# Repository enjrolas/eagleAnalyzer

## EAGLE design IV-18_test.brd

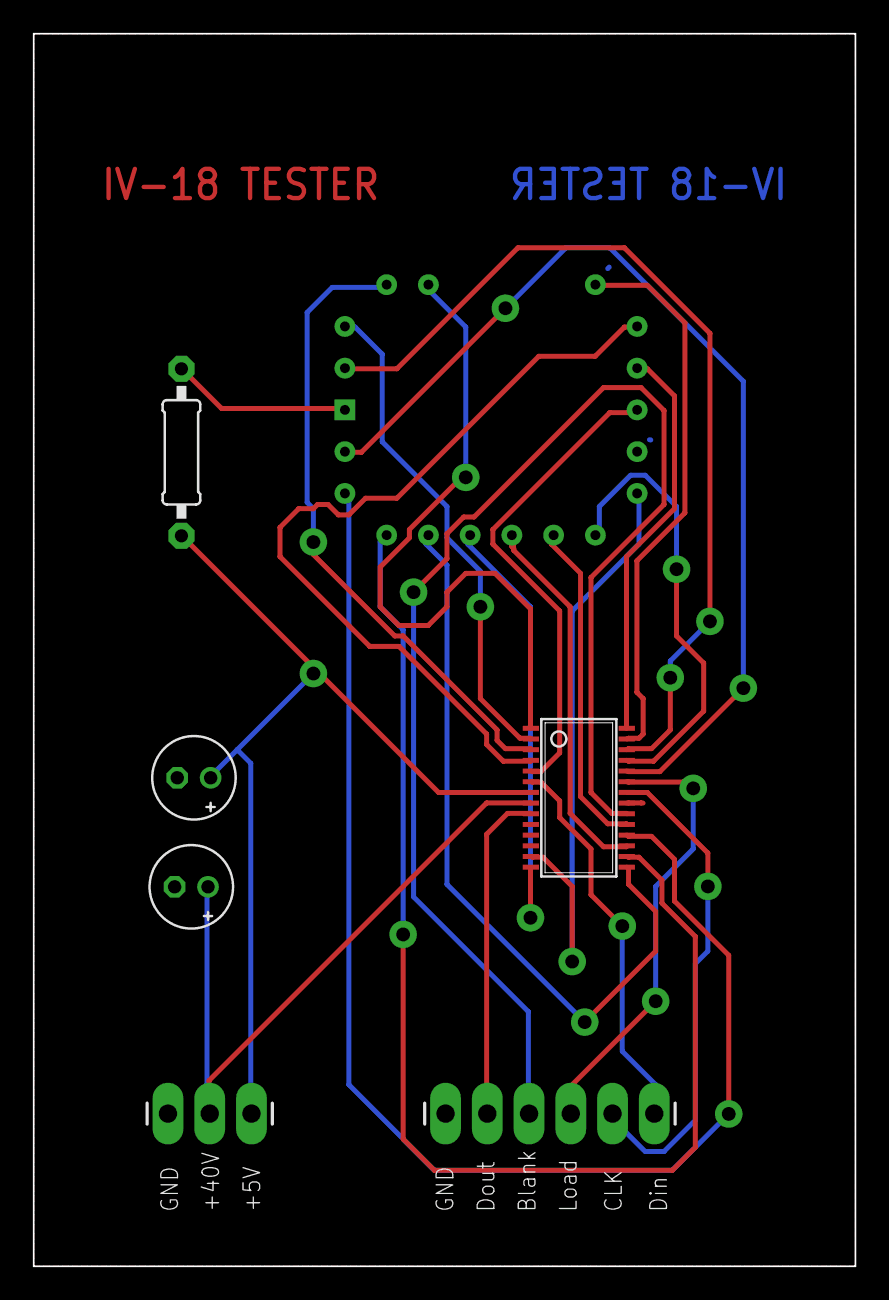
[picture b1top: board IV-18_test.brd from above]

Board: 2 copper layers, 50.0 x 75.0 mm, 7 parts (1 on the bottom side), 26 nets.

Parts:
C1: 10uF; E2-5
C2: 100nF; E2-5
DIS1: IV18-SQUARE; IV-18_SQUARE
JP1: 1X06_LONGPADS
JP2: 1X03_LONGPADS
R1: 56R; 0207/10
U$1: MAX6921AUI; TSSOP28

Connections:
GND: C1.-, C2.-, DIS1.13, JP1.1, JP2.1, U$1.21
unnamed: DIS1.12, U$1.5
unnamed: DIS1.10, U$1.4
unnamed: DIS1.4, U$1.3
unnamed: DIS1.3, U$1.2
unnamed: DIS1.5, U$1.1
unnamed: DIS1.11, U$1.28
unnamed: DIS1.9, U$1.27
unnamed: DIS1.2, U$1.26
unnamed: DIS1.15, U$1.25
unnamed: DIS1.22, U$1.24
unnamed: DIS1.16, U$1.19
unnamed: DIS1.21, U$1.18
unnamed: DIS1.17, U$1.17
unnamed: DIS1.20, U$1.16
unnamed: DIS1.19, U$1.15
unnamed: DIS1.18, U$1.14
unnamed: DIS1.14, U$1.13
unnamed: JP1.6, U$1.6
unnamed: JP1.5, U$1.22
unnamed: JP1.4, U$1.23
unnamed: JP1.3, U$1.20
unnamed: JP1.2, U$1.9
VBB: C2.+, JP2.2, U$1.8
VBIAS: DIS1.1, R1.1
VCC: C1.+, JP2.3, R1.2, U$1.7

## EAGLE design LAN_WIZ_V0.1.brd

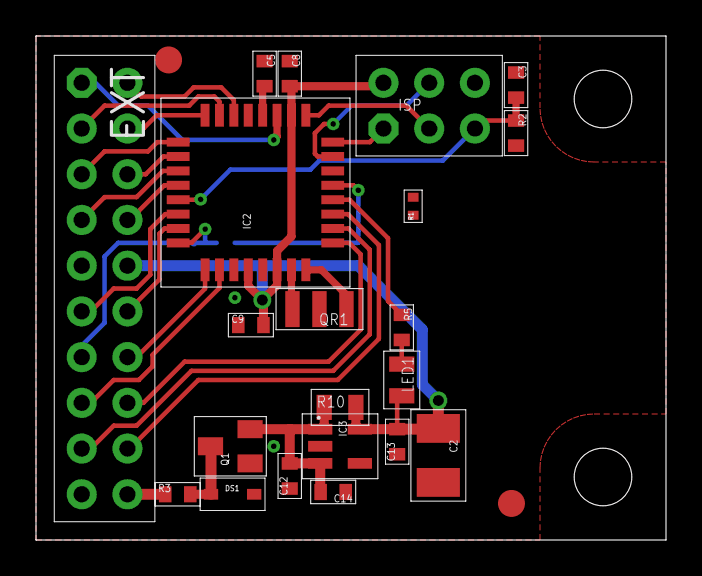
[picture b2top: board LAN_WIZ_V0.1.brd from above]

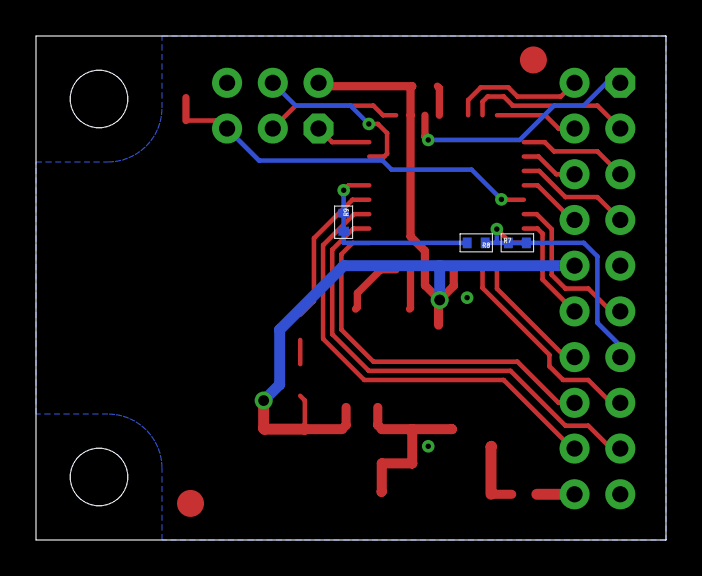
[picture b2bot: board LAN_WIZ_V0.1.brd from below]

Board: 2 copper layers, 35.0 x 28.0 mm, 26 parts (3 on the bottom side), 32 nets.

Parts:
C2: 10u; SMC_B
C3, C5, C8, C9, C14: 100n; 0603
C12, C13: 1u; 0603
DS1: PESD12VL1BA; SOD323
EXT: EXT; ML20S
IC2: MEGA328P-AU; TQFP32-08
IC3: LP2992-IM5-3.3; SOT23-5
ISP: ISP; ML6S
LED1: LEDR; 0805
Q1: IRLML9301; SOT23
QR1: 8M; CR
R1: 10k; 0402
R2: 10k; 0603
R3: 0R; 0603
R5: 330R; 0603
R7, R8, R9: 0402
R10: n.b.; 0805
U$1, U$2: FUICIDAL1.5

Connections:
+3V3: C2.+, C8.2, C9.2, C13.2, EXT.10, IC2.4, IC2.6, IC2.18, IC3.5, ISP.2, LED1.C, R1.1, R2.2, R10.2
GND: C2.-, C3.1, C5.1, C8.1, C9.1, C12.1, C13.1, C14.1, DS1.A, EXT.9, EXT.19, IC2.3, IC2.5, IC2.21, IC3.2, ISP.6, Q1.1, QR1.M
MISO: IC2.16, ISP.1
MOSI: IC2.15, ISP.4
unnamed: EXT.2, IC2.22
unnamed: DS1.C, Q1.3, R3.2
unnamed: C5.2, IC2.20
unnamed: IC2.8, QR1.1
unnamed: IC2.7, QR1.2
unnamed: EXT.20, R3.1
unnamed: IC2.12, R5.1
unnamed: EXT.13, IC2.32, R7.1, R7.2, R8.1
unnamed: C12.2, C14.2, IC3.1, IC3.3, Q1.2, R10.1
unnamed: EXT.1, IC2.19
unnamed: LED1.A, R5.2
PC0: EXT.3, IC2.23
PC1: EXT.4, IC2.24
PC2: EXT.5, IC2.25
PC3: EXT.6, IC2.26
PC4: EXT.7, IC2.27
PC5: EXT.8, IC2.28
PD3: EXT.14, IC2.1
PD4: EXT.15, IC2.2
PD5: EXT.16, IC2.9
PD6: EXT.17, IC2.10
PD7: EXT.18, IC2.11
RIRQ: IC2.13, R8.2, R9.1, R9.2
RSEL: IC2.14, R1.2
RST: C3.2, IC2.29, ISP.5, R2.1
RXD: EXT.11, IC2.30
SCK: IC2.17, ISP.3
TXD: EXT.12, IC2.31

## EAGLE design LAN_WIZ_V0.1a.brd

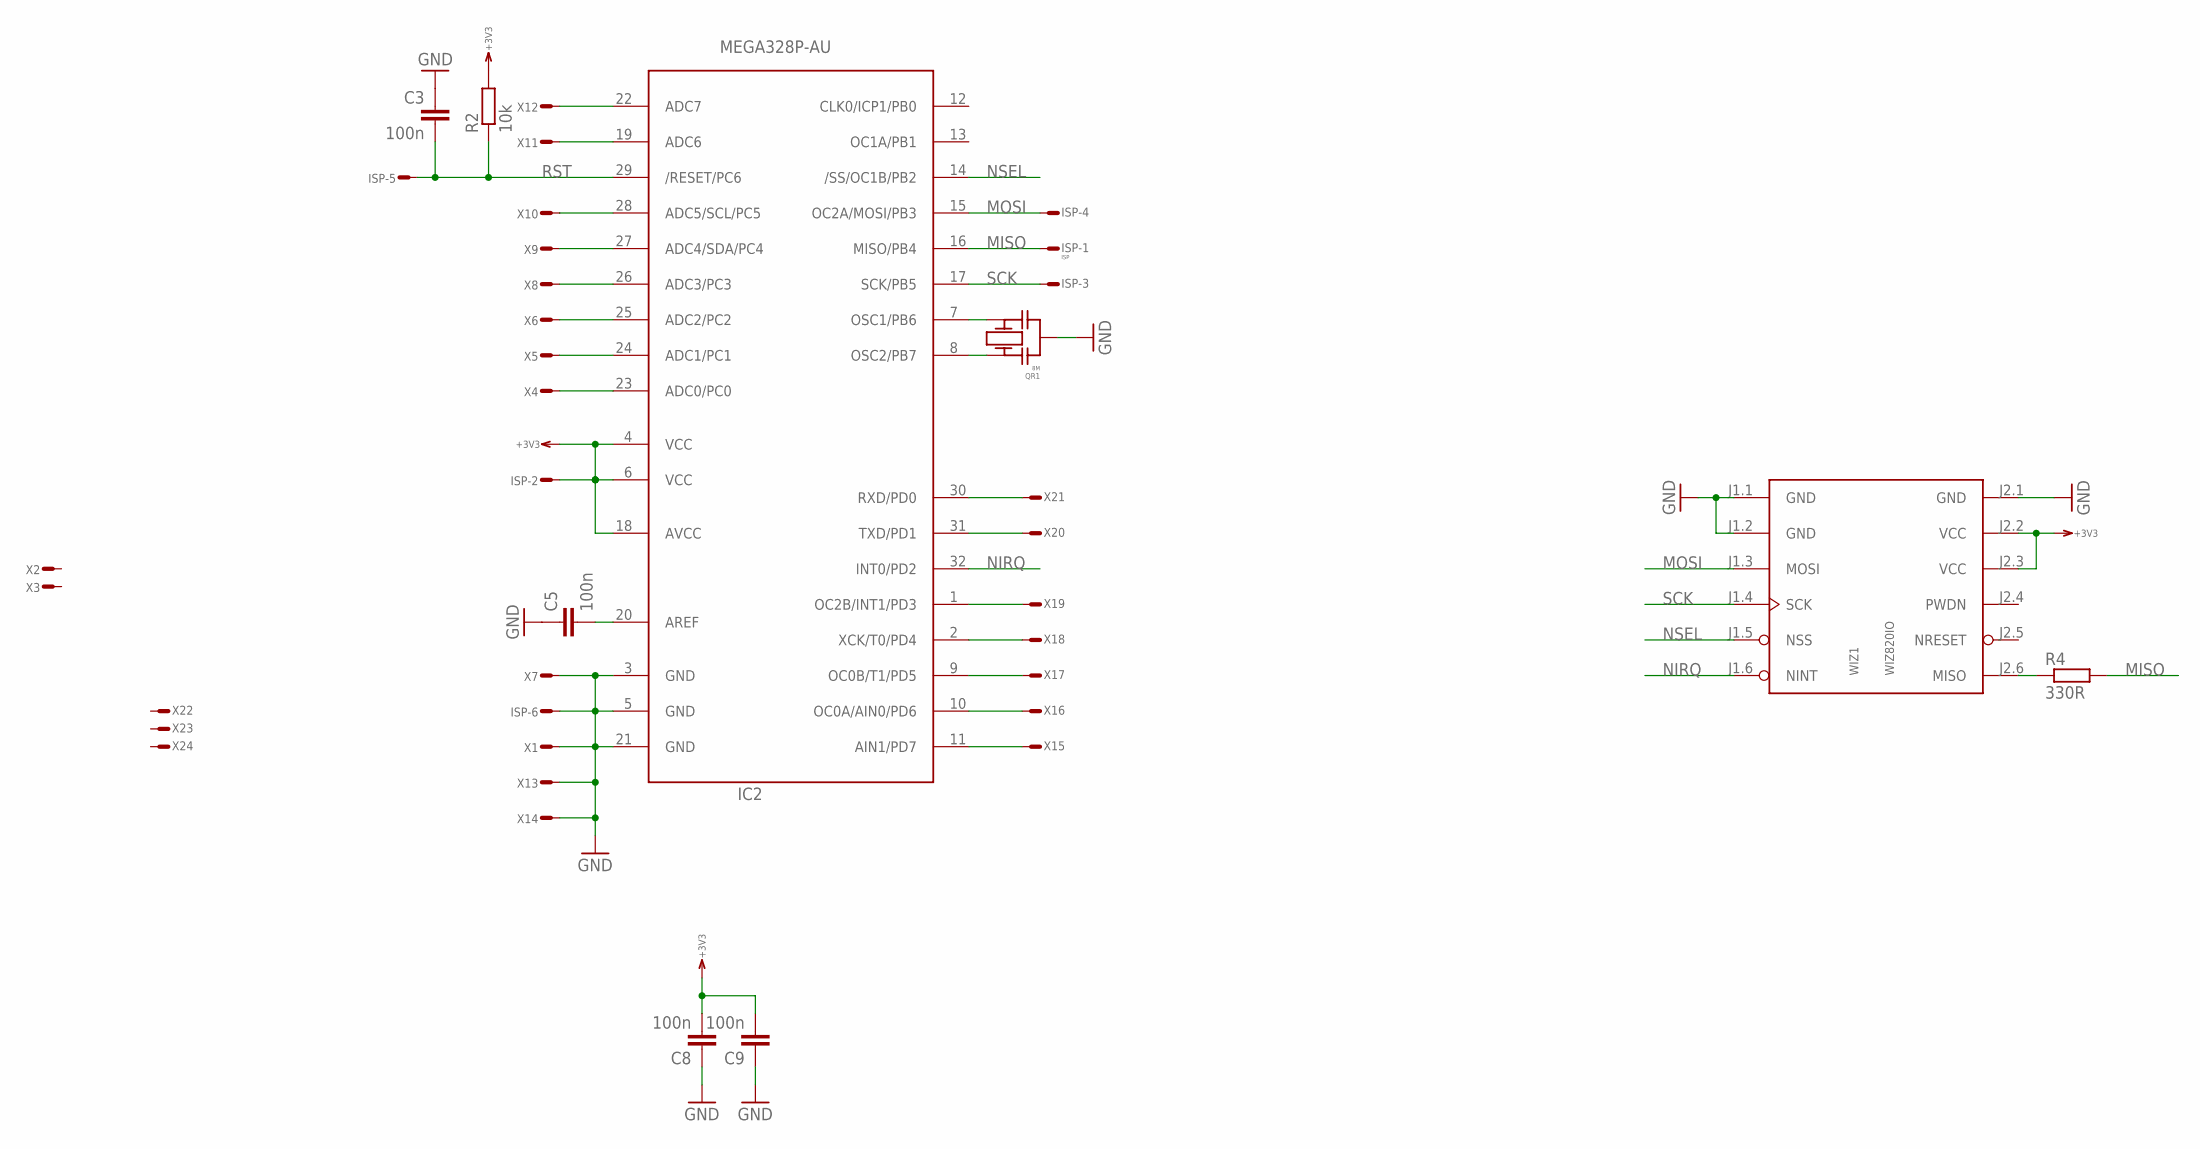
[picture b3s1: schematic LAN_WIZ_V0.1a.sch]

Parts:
C3, C5, C8, C9: 100n; 0603
IC2: MEGA328P-AU; TQFP32-08
ISP: ISP; ML6S
QR1: 8M; CR
R2: 10k; 0603
R4: 330R; 0603
WIZ1: WIZ820IO
X1, X2, X3, X4, X5, X6, X7, X8, X9, X10, X11, X12, X13, X14, X15, X16, X17, X18, X19, X20, X21, X22, X23, X24: WIREPADT1.6/0.9; T1.6/0.9

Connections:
+3V3: C8.2, C9.2, IC2.4 (VCC), IC2.6 (VCC), IC2.18 (AVCC), ISP.2, R2.2, WIZ1.J2.2 (VCC), WIZ1.J2.3 (VCC)
GND: C3.1, C5.1, C8.1, C9.1, IC2.3 (GND), IC2.5 (GND), IC2.21 (GND), ISP.6, QR1.M, WIZ1.J1.1 (GND), WIZ1.J1.2 (GND), WIZ1.J2.1 (GND), X1.1, X7.1, X13.1, X14.1
MISO: IC2.16 (MISO/PB4), ISP.1, R4.2
MOSI: IC2.15 (OC2A/MOSI/PB3), ISP.4, WIZ1.J1.3 (MOSI)
unnamed: R4.1, WIZ1.J2.6 (MISO)
unnamed: IC2.23 (ADC0/PC0), X4.1
unnamed: IC2.24 (ADC1/PC1), X5.1
unnamed: IC2.25 (ADC2/PC2), X6.1
unnamed: IC2.26 (ADC3/PC3), X8.1
unnamed: C5.2, IC2.20 (AREF)
unnamed: IC2.8 (OSC2/PB7), QR1.1
unnamed: IC2.7 (OSC1/PB6), QR1.2
unnamed: IC2.27 (ADC4/SDA/PC4), X9.1
unnamed: IC2.28 (ADC5/SCL/PC5), X10.1
unnamed: IC2.19 (ADC6), X11.1
unnamed: IC2.22 (ADC7), X12.1
unnamed: IC2.11 (AIN1/PD7), X15.1
unnamed: IC2.10 (OC0A/AIN0/PD6), X16.1
unnamed: IC2.9 (OC0B/T1/PD5), X17.1
unnamed: IC2.2 (XCK/T0/PD4), X18.1
unnamed: IC2.1 (OC2B/INT1/PD3), X19.1
unnamed: IC2.31 (TXD/PD1), X20.1
unnamed: IC2.30 (RXD/PD0), X21.1
NIRQ: IC2.32 (INT0/PD2), WIZ1.J1.6 (NINT)
NSEL: IC2.14 (/SS/OC1B/PB2), WIZ1.J1.5 (NSS)
RST: C3.2, IC2.29 (/RESET/PC6), ISP.5, R2.1
SCK: IC2.17 (SCK/PB5), ISP.3, WIZ1.J1.4 (SCK)

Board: 2 copper layers, 34 parts (0 on the bottom side), 27 nets, no tracks yet.

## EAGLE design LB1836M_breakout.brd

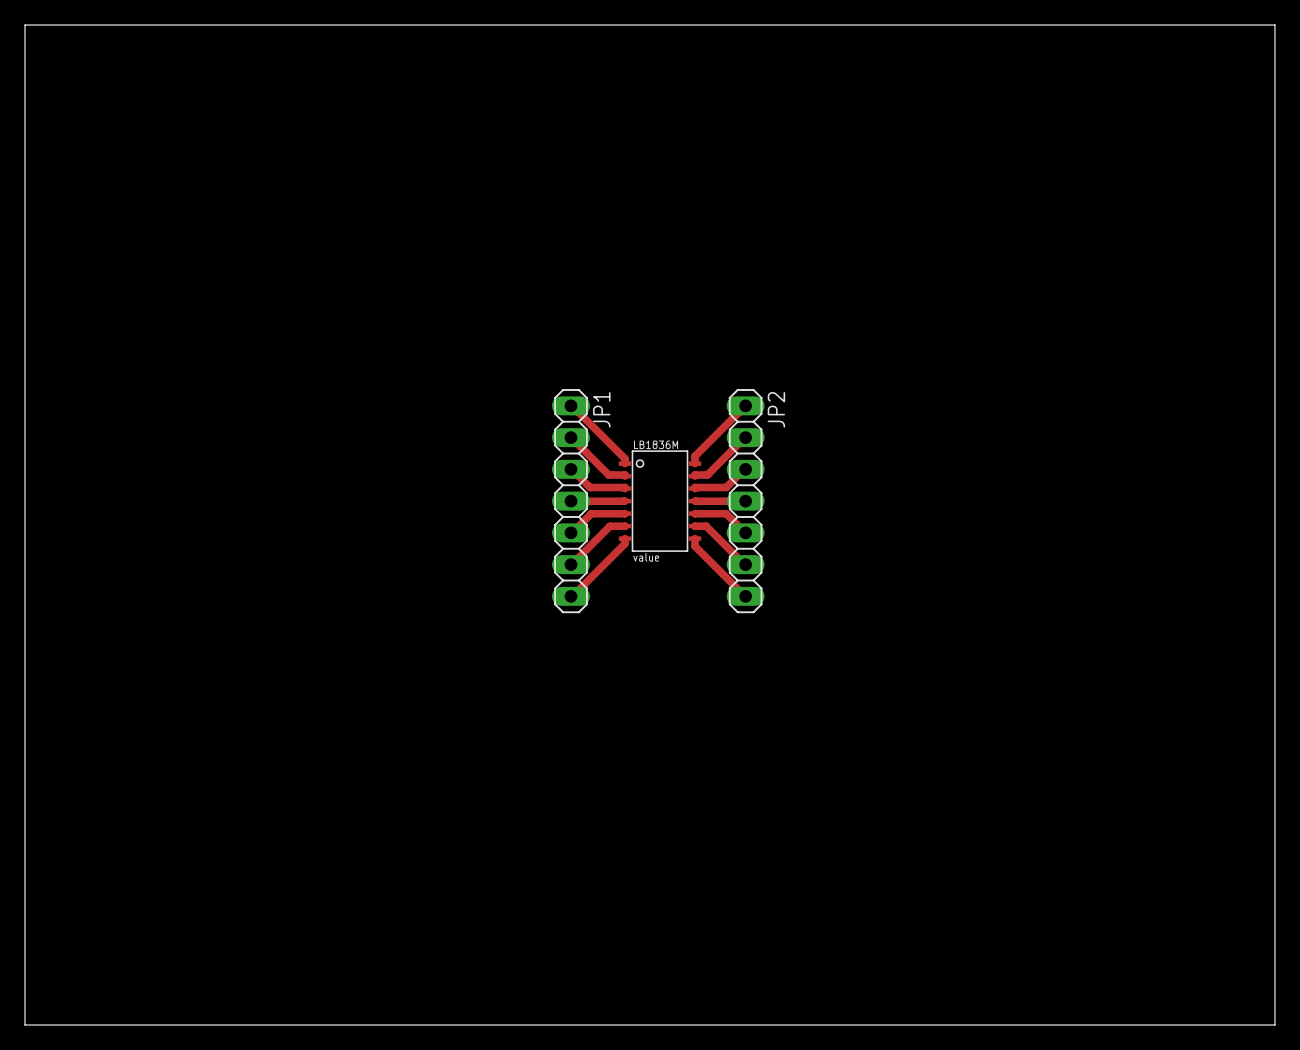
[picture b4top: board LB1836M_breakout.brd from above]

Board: 2 copper layers, 100.0 x 80.0 mm, 3 parts (0 on the bottom side), 14 nets.

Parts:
JP1, JP2: 1X07
LB1836M: LB1836M; MFP-14

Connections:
unnamed: JP2.1, LB1836M.GN2
unnamed: JP2.2, LB1836M.IN3
unnamed: JP2.3, LB1836M.OUT3
unnamed: JP2.4, LB1836M.VS2
unnamed: JP2.5, LB1836M.OUT4
unnamed: JP2.6, LB1836M.IN4
unnamed: JP2.7, LB1836M.VCONT
unnamed: JP1.1, LB1836M.VCC
unnamed: JP1.2, LB1836M.IN1
unnamed: JP1.3, LB1836M.OUT1
unnamed: JP1.4, LB1836M.VS1
unnamed: JP1.5, LB1836M.OUT2
unnamed: JP1.6, LB1836M.IN2
unnamed: JP1.7, LB1836M.GND1

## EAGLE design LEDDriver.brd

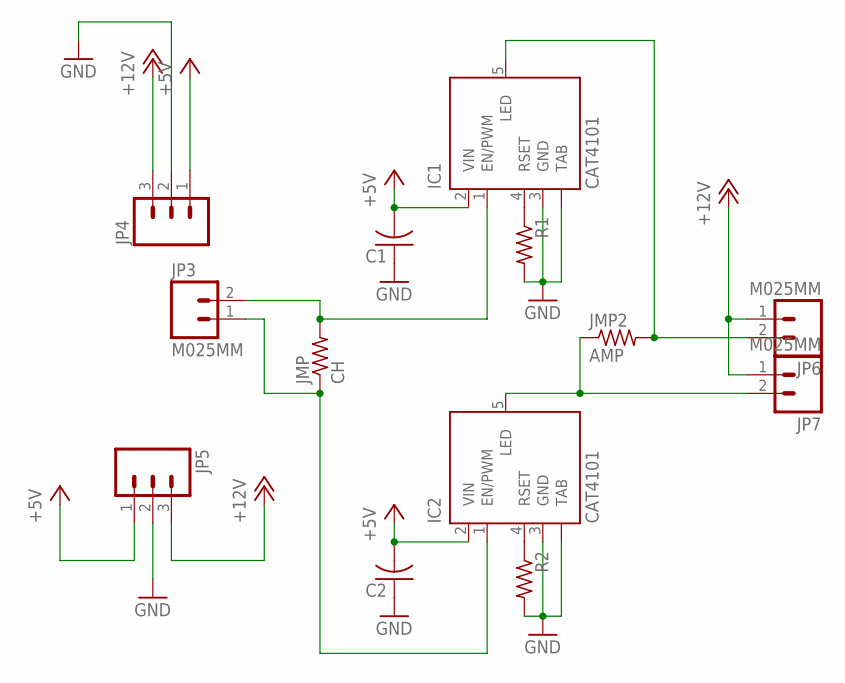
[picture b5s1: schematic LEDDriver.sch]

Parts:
C1, C2: C-USC1206; C1206
IC1, IC2: CAT4101; TO263_5
JMP: CH; R1206
JMP2: AMP; R1206
JP3, JP6, JP7: M025MM; SCREWTERMINAL-5MM-2
JP4, JP5: M03-SCREW-5MM; SCREWTERMINAL-5MM-3
R1, R2: R-US_R1206; R1206

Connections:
+5V: C1.2, C2.2, IC1.2 (VIN), IC2.2 (VIN), JP4.1, JP5.1
+12V: JP4.3, JP5.3, JP6.1, JP7.1
GND: C1.1, C2.1, IC1.3 (GND), IC1.TAB, IC2.3 (GND), IC2.TAB, JP4.2, JP5.2, R1.2, R2.2
unnamed: IC1.1 (EN/PWM), JMP.2, JP3.2
unnamed: IC2.1 (EN/PWM), JMP.1, JP3.1
unnamed: IC1.4 (RSET), R1.1
unnamed: IC2.5 (LED), JMP2.1, JP7.2
unnamed: IC1.5 (LED), JMP2.2, JP6.2
unnamed: IC2.4 (RSET), R2.1

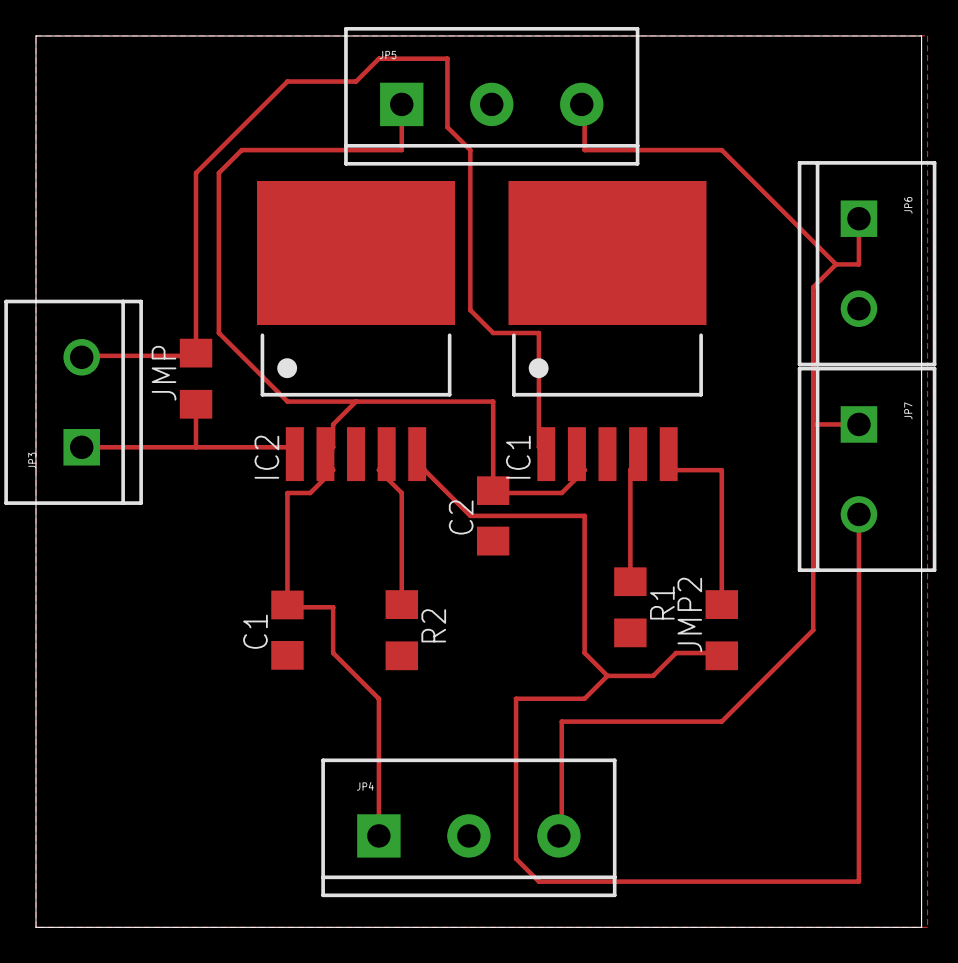
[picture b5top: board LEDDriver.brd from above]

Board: 2 copper layers, 49.2 x 49.5 mm, 13 parts (0 on the bottom side), 9 nets.

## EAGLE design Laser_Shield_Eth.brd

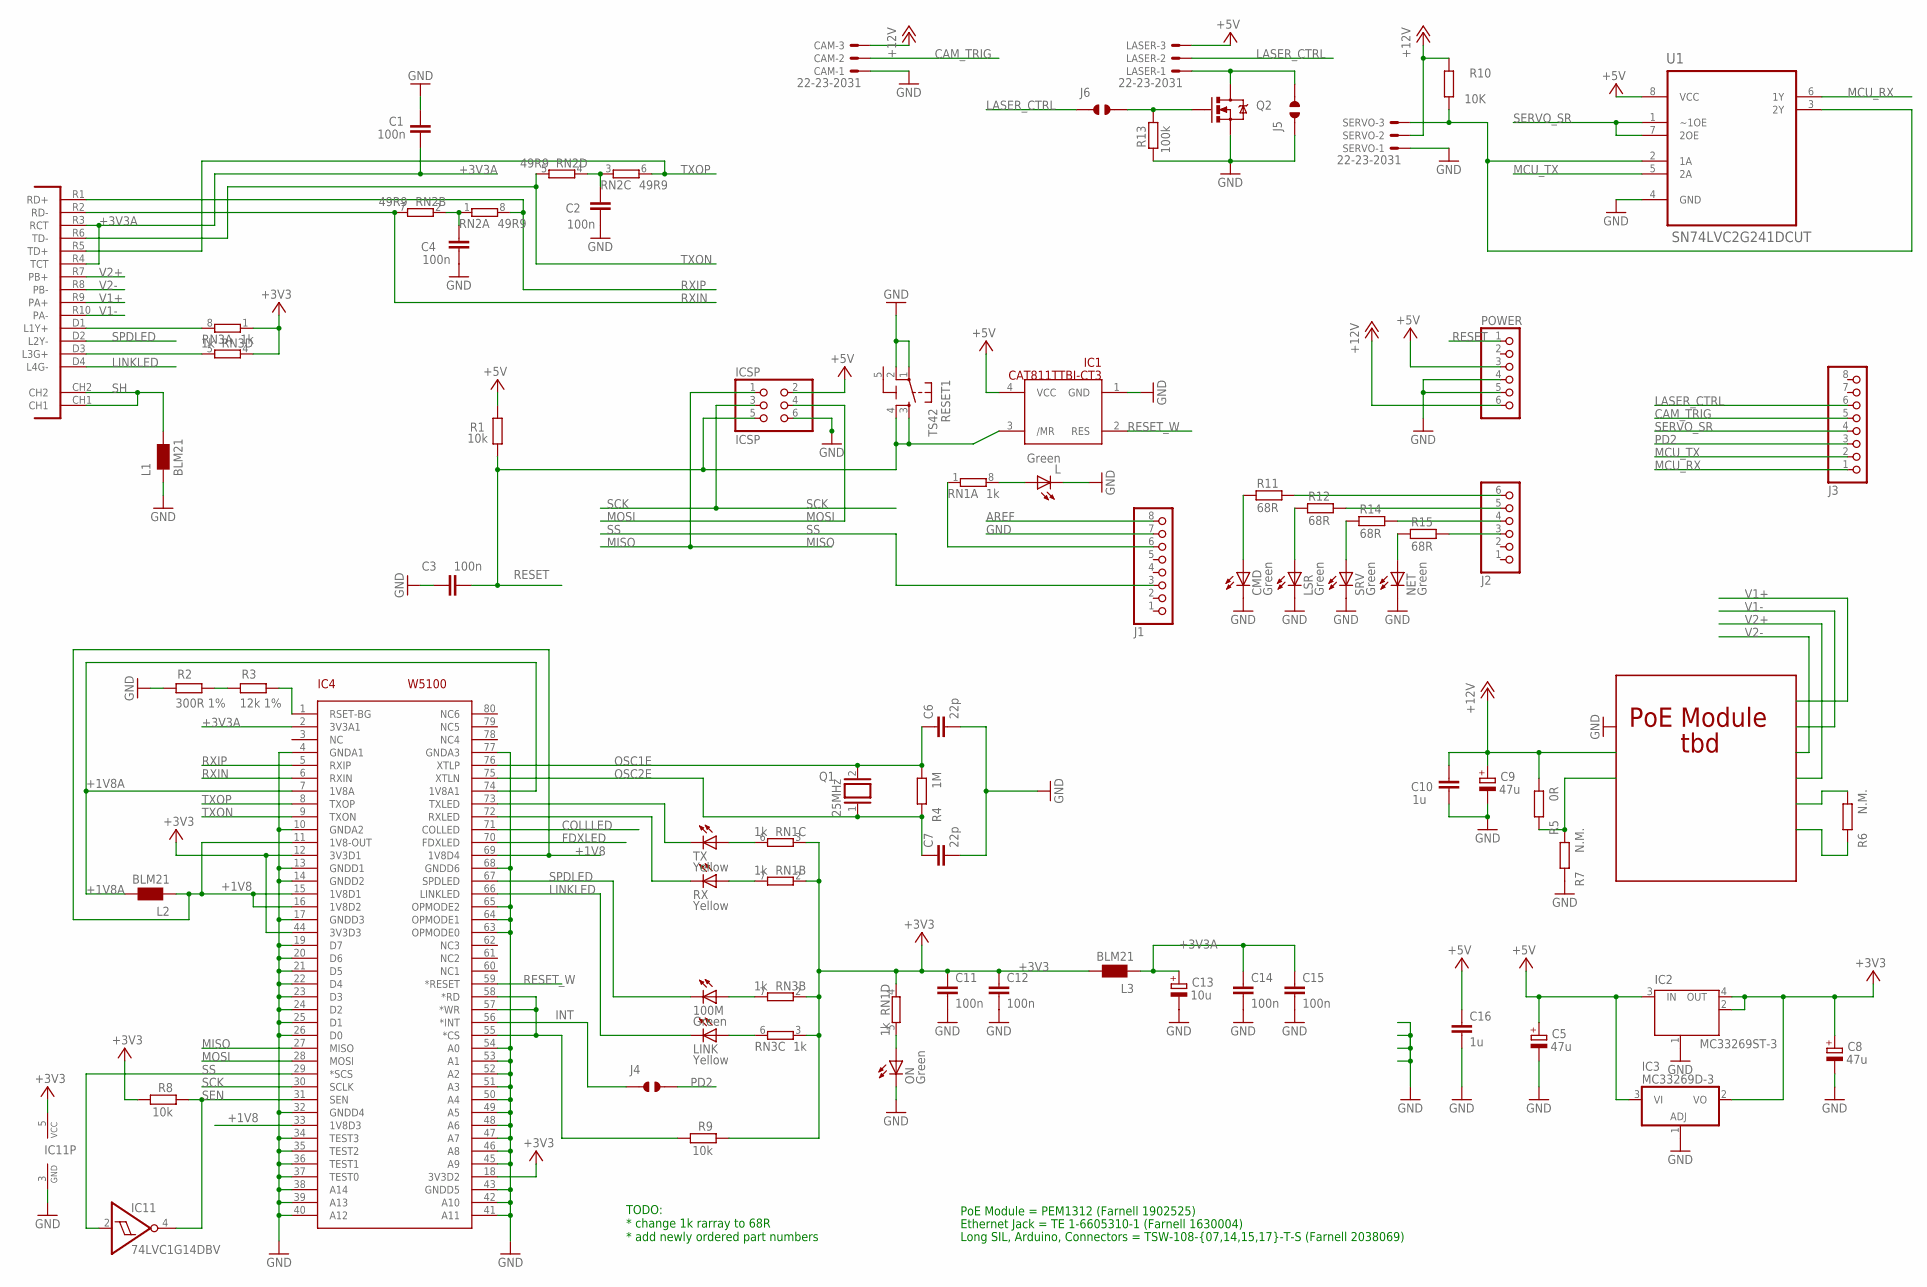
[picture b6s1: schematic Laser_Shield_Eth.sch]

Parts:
100M: Green; CHIPLED_0805
C1, C2, C3, C4, C11, C12, C14, C15: 100n; C0603-ROUND
C5, C8, C9: 47u; PANASONIC_D
C6, C7: 22p; C0603-ROUND
C10, C16: 1u; C0603-ROUND
C13: 10u; SMC_B
CAM: 22-23-2031
CMD: Green; CHIPLED_0805
IC1: CAT811TTBI-CT3; SOT143; MPN STM812LW16F
IC2: MC33269ST-3; SOT223
IC3: MC33269D-3; DPACK
IC4: W5100; SQFP-S-10X10-80
IC11: 74LVC1G14DBV; SOT23-5; MPN SN74LVC1G14DBVT
ICSP: ICSP; 2X03
J1, J3: PINHD-1X8; 1X08
J2: PINHD-1X6; 1X06
J4, J5, J6: JUMPER_SOLDER_1X2
L: Green; CHIPLED_0805
L1, L2, L3: BLM21; 0805
LASER: 22-23-2031
LINK: Yellow; CHIPLED_0805
LSR: Green; CHIPLED_0805
NET: Green; CHIPLED_0805
ON: Green; CHIPLED_0805
POWER: PINHD-1X6; 1X06
Q1: 25MHz; QS
Q2: MOSFET-NCHANNELSMD; SOT23-3
R1, R8, R9: 10k; R0603-ROUND
R2: 300R 1%; R0603-ROUND
R3: 12k 1%; R0603-ROUND
R4: 1M; R0603-ROUND
R5: 0R; R0603-ROUND
R6, R7: N.M.; R0603-ROUND
R10: 10K; R0603-ROUND
R11, R12, R14, R15: 68R; R0603-ROUND
R13: 100k; R0603-ROUND
RESET1: TS42
RN1, RN3: 1k; CAY16; MPN CAY16-102J4LF
RN2: 49R9; CAY16; MPN CAY16-49R9F4LF
RX: Yellow; CHIPLED_0805
SERVO: 22-23-2031; MPN 22-03-5035
SRV: Green; CHIPLED_0805
TX: Yellow; CHIPLED_0805
U1: SN74LVC2G241DCUT; SOP50P310X90-8N
U$1: POE-RJ45

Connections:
5-GND: RESET1.5 (5-GND)
+1V8: IC4.11 (1V8-OUT), IC4.15 (1V8D1), IC4.16 (1V8D2), IC4.33 (1V8D3), IC4.69 (1V8D4), L2.1
+1V8A: IC4.7 (1V8A), IC4.74 (1V8A1), L2.2
+3V3: C8.+, C11.1, C12.1, IC2.2 (OUT), IC2.4 (OUT), IC3.2 (VO), IC4.12 (3V3D1), IC4.18 (3V3D2), IC4.44 (3V3D3), IC11.5 (VCC), L3.2, R8.1, R9.2, RN1.2 (1), RN1.3 (1), RN1.4 (1), RN3.1, RN3.2 (1), RN3.3 (1), RN3.4 (1)
+3V3A: C1.1, C13.+, C14.1, C15.1, IC4.2 (3V3A1), L3.1, U$1.R3 (RCT), U$1.R4 (TCT)
+5V: C5.+, C16.1, IC1.4 (VCC), IC2.3 (IN), IC3.3 (VI), ICSP.2, LASER.3, POWER.3, R1.2, U1.8 (VCC)
+12V: C9.+, C10.2, CAM.3, POWER.6, R5.1, R10.1, SERVO.2
AREF: J1.8
CAM_TRIG: CAM.2, J3.5
COLLLED: IC4.71 (COLLED)
FDXLED: IC4.70 (FDXLED)
GND: C1.2, C2.1, C3.2, C4.1, C5.-, C6.2, C7.2, C8.-, C9.-, C10.1, C11.2, C12.2, C13.-, C14.2, C15.2, C16.2, CAM.1, CMD.C, IC1.1 (GND), IC2.1 (GND/ADJ), IC3.1 (ADJ), IC4.4 (GNDA1), IC4.10 (GNDA2), IC4.13 (GNDD1), IC4.14 (GNDD2), IC4.17 (GNDD3), IC4.19 (D7), IC4.20 (D6), IC4.21 (D5), IC4.22 (D4), IC4.23 (D3), IC4.24 (D2), IC4.25 (D1), IC4.26 (D0), IC4.32 (GNDD4), IC4.34 (TEST3), IC4.35 (TEST2), IC4.36 (TEST1), IC4.37 (TEST0), IC4.38 (A14), IC4.39 (A13), IC4.40 (A12), IC4.41 (A11), IC4.42 (A10), IC4.43 (GNDD5), IC4.45 (A9), IC4.46 (A8), IC4.47 (A7), IC4.48 (A6), IC4.49 (A5), IC4.50 (A4), IC4.51 (A3), IC4.52 (A2), IC4.53 (A1), IC4.54 (A0), IC4.63 (OPMODE0), IC4.64 (OPMODE1), IC4.65 (OPMODE2), IC4.68 (GNDD6), IC4.77 (GNDA3), IC11.3 (GND), ICSP.6, J1.7, J5.1, L.C, L1.1, LSR.C, NET.C, ON.C, POWER.4, POWER.5, Q2.2 (S), R2.2, R7.2, R13.1, RESET1.1, RESET1.2, SERVO.1, SRV.C, U1.4 (GND)
INT: IC4.56 (*INT), J4.1
LASER_CTRL: J3.6, J6.1, LASER.2
LINKLED: IC4.66 (LINKLED), LINK.C, U$1.D4 (L4G-)
MCU_RX: J3.1, U1.6 (1Y)
MCU_TX: J3.2, U1.5 (2A)
MISO: IC4.27 (MISO), ICSP.1
MOSI: IC4.28 (MOSI), ICSP.4
unnamed: L.A, RN1.8 (2)
unnamed: RN3.5 (2), U$1.D3 (L3G+)
unnamed: RN3.8 (2), U$1.D1 (L1Y+)
unnamed: CMD.A, R11.1
unnamed: LSR.A, R12.1
unnamed: IC4.73 (TXLED), TX.C
unnamed: IC4.72 (RXLED), RX.C
unnamed: ON.A, RN1.5 (2)
unnamed: RN1.6 (2), TX.A
unnamed: C2.2, RN2.3 (1), RN2.4 (1)
unnamed: R14.1, SRV.A
unnamed: NET.A, R15.1
unnamed: J6.2, Q2.1 (G), R13.2
unnamed: J5.2, LASER.1, Q2.3 (D)
unnamed: J1.6, RN1.1
unnamed: J2.6, R11.2
unnamed: J2.5, R12.2
unnamed: J2.4, R14.2
unnamed: J2.3, R15.2
unnamed: RN1.7 (2), RX.A
unnamed: 100M.A, RN3.7 (2)
unnamed: LINK.A, RN3.6 (2)
unnamed: C4.2, RN2.1, RN2.2 (1)
unnamed: R2.1, R3.2
unnamed: IC4.1 (RSET-BG), R3.1
unnamed: R5.2, R7.1
unnamed: IC4.55 (*CS), IC4.57 (*WR), IC4.58 (*RD), R9.1
OSC1E: C6.1, IC4.76 (XTLP), Q1.2, R4.1
OSC2E: C7.1, IC4.75 (XTLN), Q1.1, R4.2
PD2: J3.3, J4.2
RESET: C3.1, IC1.3 (/MR), ICSP.5, POWER.1, R1.1, RESET1.3, RESET1.4
RESET_W: IC1.2 (RES), IC4.59 (*RESET)
RXIN: IC4.6 (RXIN), RN2.7 (2), U$1.R2 (RD-)
RXIP: IC4.5 (RXIP), RN2.8 (2), U$1.R1 (RD+)
SCK: IC4.30 (SCLK), ICSP.3
SEN: IC4.31 (SEN), IC11.4 (O), R8.2
SERVO_DATA: R10.2, SERVO.3, U1.2 (1A), U1.3 (2Y)
SERVO_SR: J3.4, U1.1 (~1OE), U1.7 (2OE)
SH: L1.2, U$1.CH1, U$1.CH2
SPDLED: 100M.C, IC4.67 (SPDLED), U$1.D2 (L2Y-)
SS: IC4.29 (*SCS), IC11.2 (I), J1.3
TXON: IC4.9 (TXON), RN2.5 (2), U$1.R6 (TD-)
TXOP: IC4.8 (TXOP), RN2.6 (2), U$1.R5 (TD+)
V1+: U$1.R9 (PA+)
V1-: U$1.R10 (PA-)
V2+: U$1.R7 (PB+)
V2-: U$1.R8 (PB-)

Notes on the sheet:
PoE Module
tbd
PoE Module = PEM1312 (Farnell 1902525)
Ethernet Jack = TE 1-6605310-1 (Farnell 1630004)
Long SIL, Arduino, Connectors = TSW-108-{07,14,15,17}-T-S (Farnell 2038069)
TODO: * change 1k rarray to 68R * add newly ordered part numbers

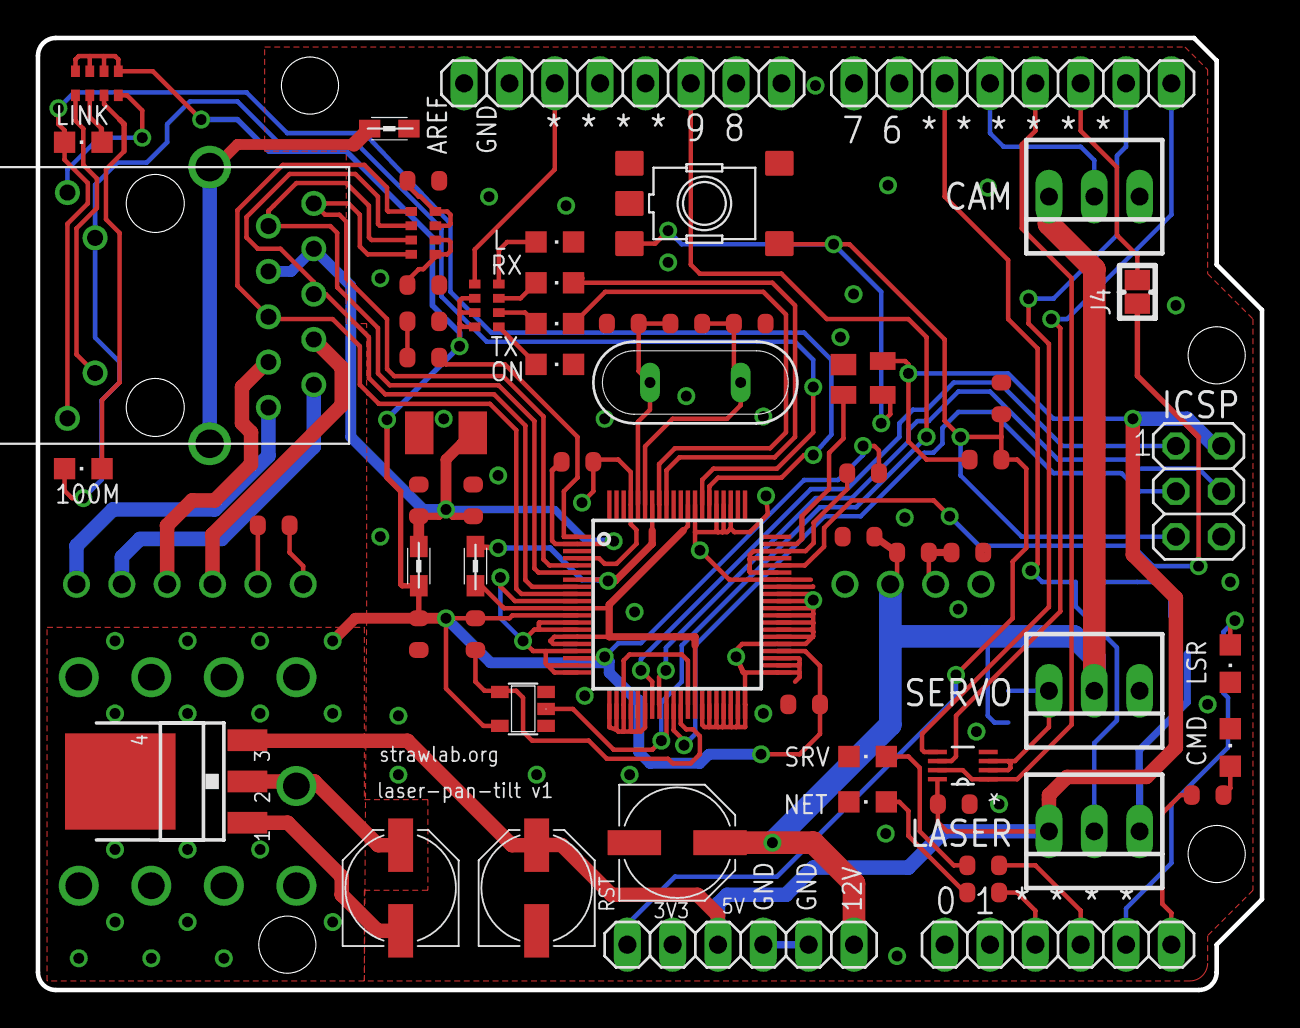
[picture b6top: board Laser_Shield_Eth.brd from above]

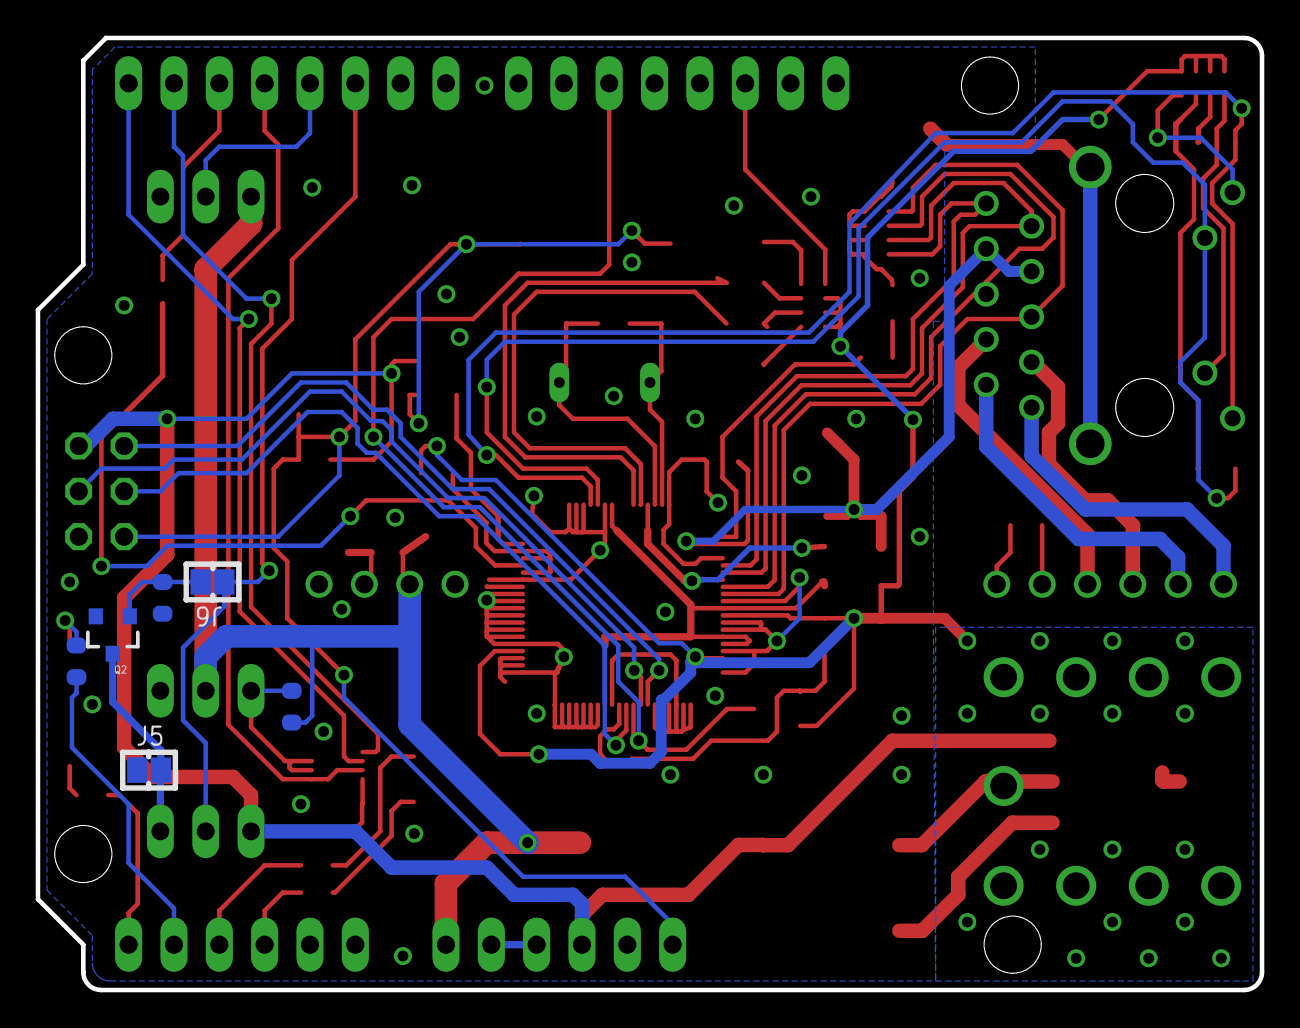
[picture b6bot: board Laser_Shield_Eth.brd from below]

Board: 2 copper layers, 68.6 x 53.3 mm, 68 parts (6 on the bottom side), 58 nets.

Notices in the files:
parts and their libraries:
SparkFun-Connectors: Licensing: CC v3.0 Share-Alike You are welcome to use this library for commercial purposes.
